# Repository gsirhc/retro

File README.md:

# retro

> **Read-only.** This repo is archived. The browser emulators moved to
> [gsirhc/oac-emu](https://github.com/gsirhc/oac-emu), live at
> <https://gsirhc.github.io/oac-emu/>. This copy is kept for its history.

Recreations of vintage machines, faithful to the real hardware.

## `retroweb/` — the browser emulators

A static site: [`retroweb/index.html`](retroweb/index.html) is the landing page,
each machine is a subdirectory.

| Machine | Source | Deployed at |
|---|---|---|
| **MITS Altair 8800** (Intel 8080, CP/M 2.2, Altair BASIC) | [`retroweb/altair8800/`](retroweb/altair8800/) | `/altair8800/` |

The Altair project is the shared C++ 8080 core (`retroweb/shared/cpu/cpu_i8080`, also
used by Space Invaders) plus 88-2SIO, 88-ACR cassette,
88-DCDD floppy) with a GoogleTest suite, compiled to WebAssembly and wired to an
xterm.js front end in `retroweb/altair8800/web/`. See its
[README](retroweb/altair8800/README.md).

CI (`.github/workflows/deploy-emulator.yml`) runs the C++ and Playwright suites,
stages the site (`retroweb/index.html` at the root, the built front end under
`/altair8800/`), and publishes it to GitHub Pages. It does not deploy a red
build.

## Other directories

`cpu6502`, `commodore64`, `cc65`, `kicad` — earlier / adjacent experiments.

## Provenance

Some earlier commits contained code taken from other emulators. See
[PROVENANCE.md](PROVENANCE.md) for what, and what replaced it.

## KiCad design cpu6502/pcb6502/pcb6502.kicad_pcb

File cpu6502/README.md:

# Programming 6502

## Links

Compiler: <http://www.compilers.de/vasm.html>

Programmer: <https://gitlab.com/DavidGriffith/minipro> (Install with brew)

## Setup

1. Unzip `vasm6502.zip` to .
2. Install minipro (see links above)

## Programming EEPROM

1. Create the assembly file (asm)
2. Compile the assembly:

   `./vasm6502_oldstyle/vasm6502_oldstyle test/ImAlive.asm -dotdir -Fbin`
3. Can check binary with:

   `hexdump -C a.out`
4. Send to programmer:

   `minipro -p AT28C256 -w a.out`
5. You can run:

   `sh compile.sh HellowWorld.asm`

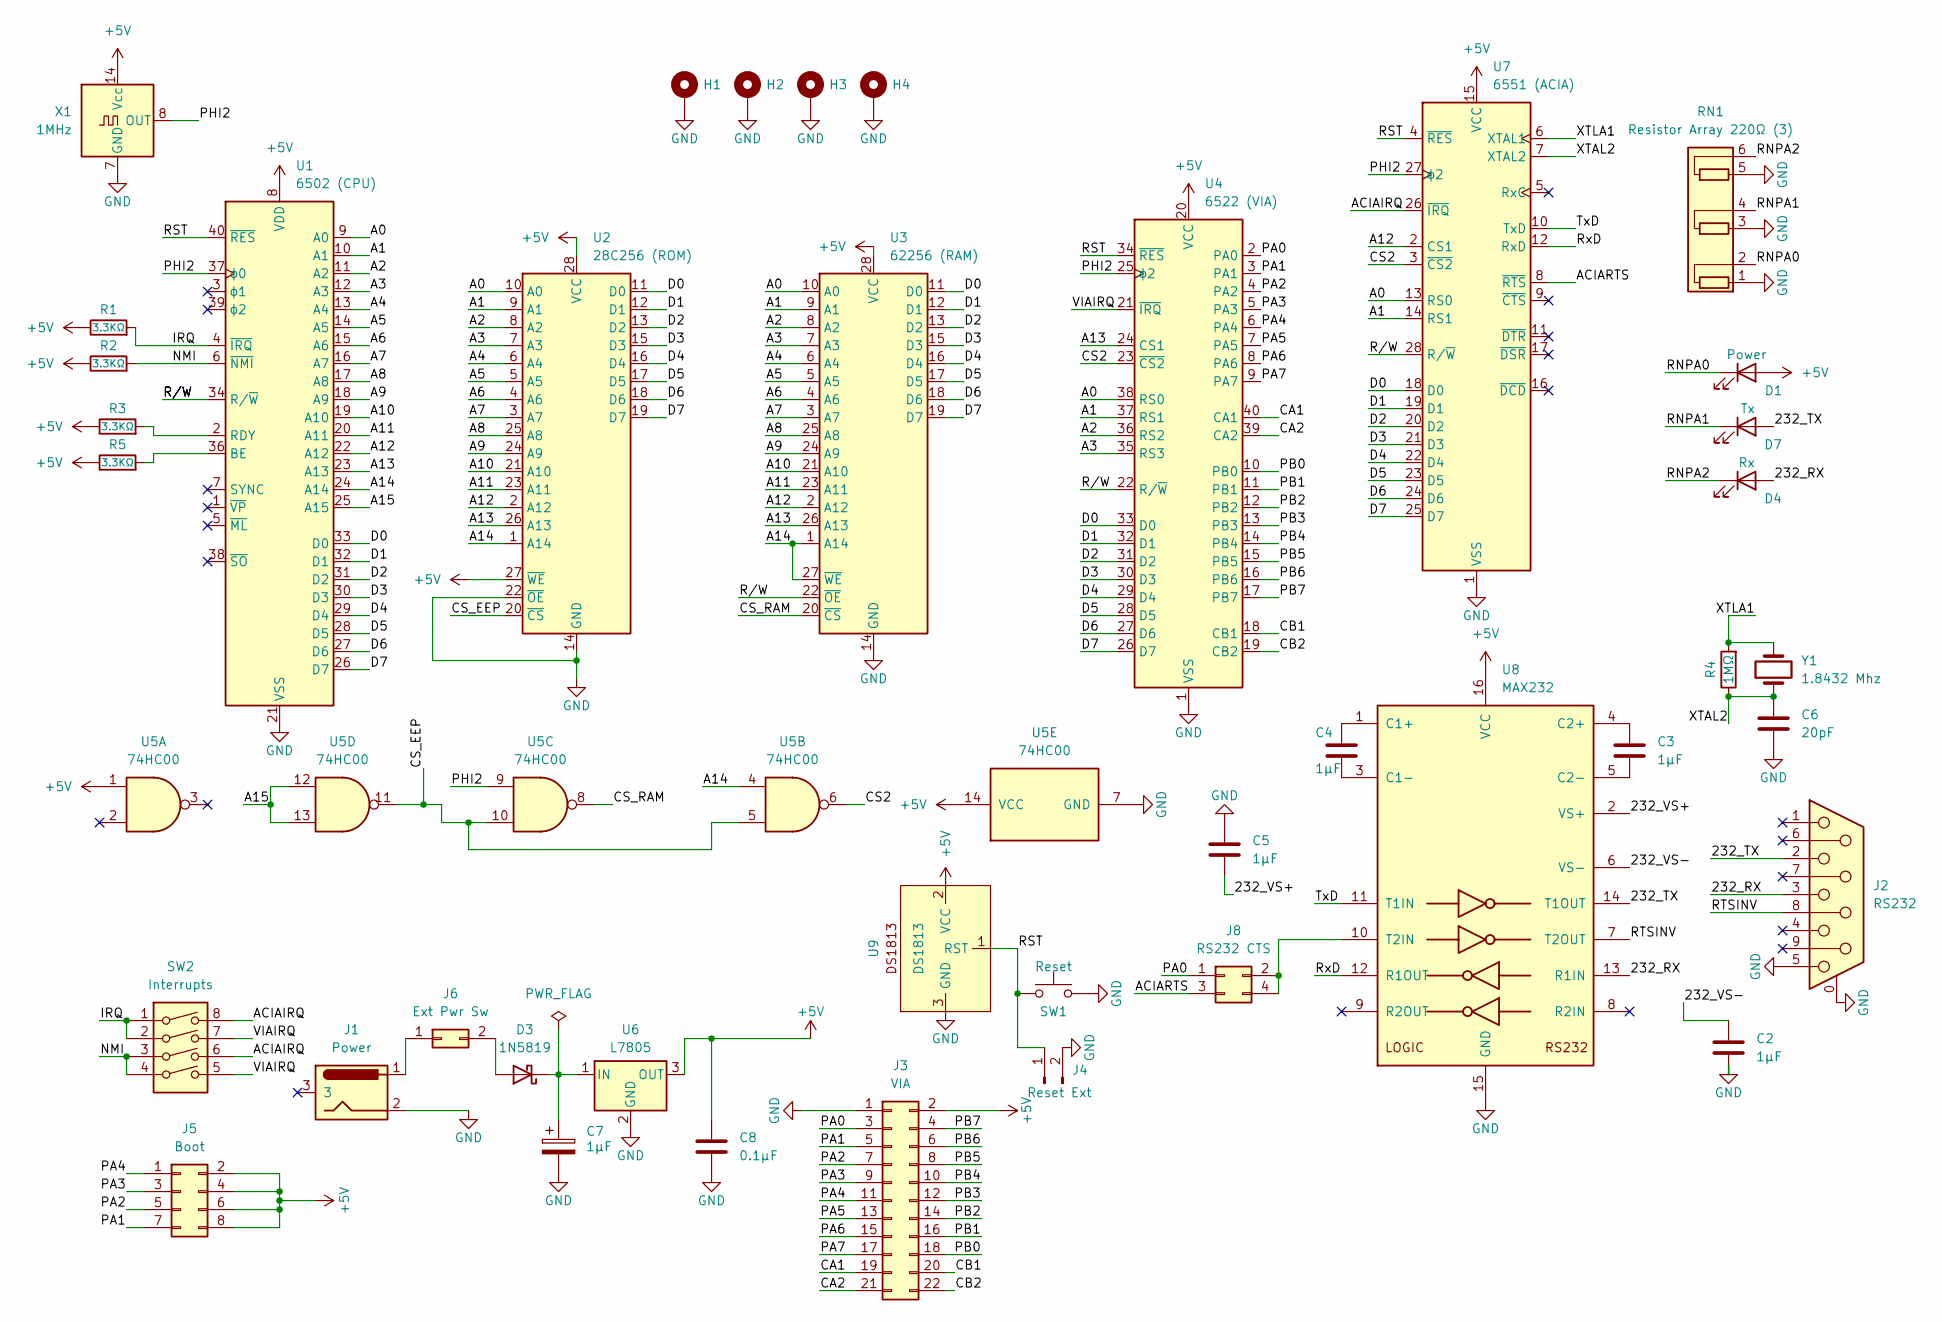
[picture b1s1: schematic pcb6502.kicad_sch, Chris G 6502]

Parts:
C2, C3, C4, C5: 1µF; C_Disc_D5.0mm_W2.5mm_P5.00mm
C6: 20pF; C_Disc_D5.0mm_W2.5mm_P5.00mm
C7: 1µF; CP_Radial_D5.0mm_P2.50mm
C8: 0.1µF; C_Disc_D3.0mm_W1.6mm_P2.50mm
D1: Power; LED_D3.0mm
D3: 1N5819; D_DO-41_SOD81_P10.16mm_Horizontal
D4: Rx; LED_D3.0mm
D7: Tx; LED_D3.0mm
H1, H2, H3, H4: MountingHole_3.2mm_M3_Pad_Via
J1: Power; BarrelJack_Horizontal
J2: RS232; DSUB-9_Male_Horizontal_P2.77x2.84mm_EdgePinOffset4.94mm_Hou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
J3: VIA; PinHeader_2x11_P2.54mm_Vertical
J4: Reset Ext; PinHeader_1x02_P2.54mm_Vertical
J5: Boot; PinHeader_2x04_P2.54mm_Vertical
J6: Ext Pwr Sw; PinHeader_2x01_P2.54mm_Vertical
J8: RS232 CTS; PinHeader_2x02_P2.54mm_Vertical
R1, R2, R3, R5: 3.3KΩ; R_Axial_DIN0204_L3.6mm_D1.6mm_P7.62mm_Horizontal
R4: 1MΩ; R_Axial_DIN0204_L3.6mm_D1.6mm_P7.62mm_Horizontal
RN1: Resistor Array 220Ω (3); R_Array_SIP6
SW1: Reset; SW_TH_Tactile_Omron_B3F-10xx
SW2: Interrupts; SW_DIP_SPSTx04_Slide_9.78x12.34mm_W7.62mm_P2.54mm
U1: 6502 (CPU); DIP-40_W15.24mm_Socket
U2: 28C256 (ROM); DIP-28_600_ZIF_ARIES_28-526-10
U3: 62256 (RAM); DIP-28_W15.24mm_Socket
U4: 6522 (VIA); DIP-40_W15.24mm_Socket
U5: 74HC00; DIP-14_W7.62mm_Socket
U6: L7805; TO-220-3_Horizontal_TabDown
U7: 6551 (ACIA); DIP-28_W15.24mm_Socket
U8: MAX232; DIP-16_W7.62mm_Socket
U9: DS1813; TO-92
X1: 1MHz; Oscillator_DIP-14
Y1: 1.8432 Mhz; Crystal_HC49-4H_Vertical

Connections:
+5V: C8.1, D1.2 (A), J3.2, J5.2, J5.4, J5.6, J5.8, R1.1, R2.1, R3.1, R5.1, U1.8 (VDD), U2.27 (~WE), U2.28 (VCC), U3.28 (VCC), U4.20 (VCC), U5.1, U5.14 (VCC), U6.3 (OUT), U7.15 (VCC), U8.16 (VCC), U9.2 (VCC), X1.14 (Vcc)
/232_RX: D4.2 (A), J2.3, U8.13 (R1IN)
/232_TX: D7.2 (A), J2.2, U8.14 (T1OUT)
/232_VS+: C5.2, U8.2 (VS+)
/232_VS-: C2.1, U8.6 (VS-)
/A0: U1.9 (A0), U2.10 (A0), U3.10 (A0), U4.38 (RS0), U7.13 (RS0)
/A1: U1.10 (A1), U2.9 (A1), U3.9 (A1), U4.37 (RS1), U7.14 (RS1)
/A2: U1.11 (A2), U2.8 (A2), U3.8 (A2), U4.36 (RS2)
/A3: U1.12 (A3), U2.7 (A3), U3.7 (A3), U4.35 (RS3)
/A4: U1.13 (A4), U2.6 (A4), U3.6 (A4)
/A5: U1.14 (A5), U2.5 (A5), U3.5 (A5)
/A6: U1.15 (A6), U2.4 (A6), U3.4 (A6)
/A7: U1.16 (A7), U2.3 (A7), U3.3 (A7)
/A8: U1.17 (A8), U2.25 (A8), U3.25 (A8)
/A9: U1.18 (A9), U2.24 (A9), U3.24 (A9)
/A10: U1.19 (A10), U2.21 (A10), U3.21 (A10)
/A11: U1.20 (A11), U2.23 (A11), U3.23 (A11)
/A12: U1.22 (A12), U2.2 (A12), U3.2 (A12), U7.2 (CS1)
/A13: U1.23 (A13), U2.26 (A13), U3.26 (A13), U4.24 (CS1)
/A14: U1.24 (A14), U2.1 (A14), U3.1 (A14), U3.27 (~WE), U5.4
/A15: U1.25 (A15), U5.12, U5.13
/ACIAIRQ: SW2.6, SW2.8, U7.26 (~IRQ)
/ACIARTS: J8.3, U7.8 (~RTS)
/CA1: J3.19, U4.40 (CA1)
/CA2: J3.21, U4.39 (CA2)
/CB1: J3.20, U4.18 (CB1)
/CB2: J3.22, U4.19 (CB2)
/CS2: U4.23 (~CS2), U5.6, U7.3 (~CS2)
/CS_EEP: U2.20 (~CS), U5.5, U5.10, U5.11
/CS_RAM: U3.20 (~CS), U5.8
/D0: U1.33 (D0), U2.11 (D0), U3.11 (D0), U4.33 (D0), U7.18 (D0)
/D1: U1.32 (D1), U2.12 (D1), U3.12 (D1), U4.32 (D1), U7.19 (D1)
/D2: U1.31 (D2), U2.13 (D2), U3.13 (D2), U4.31 (D2), U7.20 (D2)
/D3: U1.30 (D3), U2.15 (D3), U3.15 (D3), U4.30 (D3), U7.21 (D3)
/D4: U1.29 (D4), U2.16 (D4), U3.16 (D4), U4.29 (D4), U7.22 (D4)
/D5: U1.28 (D5), U2.17 (D5), U3.17 (D5), U4.28 (D5), U7.23 (D5)
/D6: U1.27 (D6), U2.18 (D6), U3.18 (D6), U4.27 (D6), U7.24 (D6)
/D7: U1.26 (D7), U2.19 (D7), U3.19 (D7), U4.26 (D7), U7.25 (D7)
/IRQ: R1.2, SW2.1, SW2.2, U1.4 (~IRQ)
/NMI: R2.2, SW2.3, SW2.4, U1.6 (~NMI)
/PA0: J3.3, J8.1, U4.2 (PA0)
/PA1: J3.5, J5.7, U4.3 (PA1)
/PA2: J3.7, J5.5, U4.4 (PA2)
/PA3: J3.9, J5.3, U4.5 (PA3)
/PA4: J3.11, J5.1, U4.6 (PA4)
/PA5: J3.13, U4.7 (PA5)
/PA6: J3.15, U4.8 (PA6)
/PA7: J3.17, U4.9 (PA7)
/PB0: J3.18, U4.10 (PB0)
/PB1: J3.16, U4.11 (PB1)
/PB2: J3.14, U4.12 (PB2)
/PB3: J3.12, U4.13 (PB3)
/PB4: J3.10, U4.14 (PB4)
/PB5: J3.8, U4.15 (PB5)
/PB6: J3.6, U4.16 (PB6)
/PB7: J3.4, U4.17 (PB7)
/PHI2: U1.37 (ϕ0), U4.25 (ϕ2), U5.9, U7.27 (ϕ2), X1.8 (OUT)
/RNPA0: D1.1 (K), RN1.2 (R1.2)
/RNPA1: D7.1 (K), RN1.4 (R2.2)
/RNPA2: D4.1 (K), RN1.6 (R3.2)
/RST: J4.1, SW1.1, U1.40 (~RES), U4.34 (~RES), U7.4 (~RES), U9.1 (RST)
/RTSINV: J2.8, U8.7 (T2OUT)
/RxD: U7.12 (RxD), U8.12 (R1OUT)
/R/W: U1.34 (R/~W), U3.22 (~OE), U4.22 (R/~W), U7.28 (R/~W)
/TxD: U7.10 (TxD), U8.11 (T1IN)
/VIAIRQ: SW2.5, SW2.7, U4.21 (~IRQ)
/XTAL2: C6.1, R4.1, U7.7 (XTAL2), Y1.1
/XTLA1: R4.2, U7.6 (XTAL1), Y1.2
GND: C2.2, C5.1, C6.2, C7.2, C8.2, H1.1, H2.1, H3.1, H4.1, J1.2, J2.0 (PAD), J2.5, J3.1, J4.2, RN1.1 (R1.1), RN1.3 (R2.1), RN1.5 (R3.1), SW1.2, U1.21 (VSS), U2.14 (GND), U2.22 (~OE), U3.14 (GND), U4.1 (VSS), U5.7 (GND), U6.2 (GND), U7.1 (VSS), U8.15 (GND), U9.3 (GND), X1.7 (GND)
unnamed: D3.2 (A), J6.2
unnamed: C7.1, D3.1 (K), U6.1 (IN)
unnamed: J1.1, J6.1
unnamed: J8.2, J8.4, U8.10 (T2IN)
unnamed: R5.2, U1.36 (BE)
unnamed: R3.2, U1.2 (RDY)
unnamed: C4.1, U8.1 (C1+)
unnamed: C4.2, U8.3 (C1-)
unnamed: C3.1, U8.4 (C2+)
unnamed: C3.2, U8.5 (C2-)

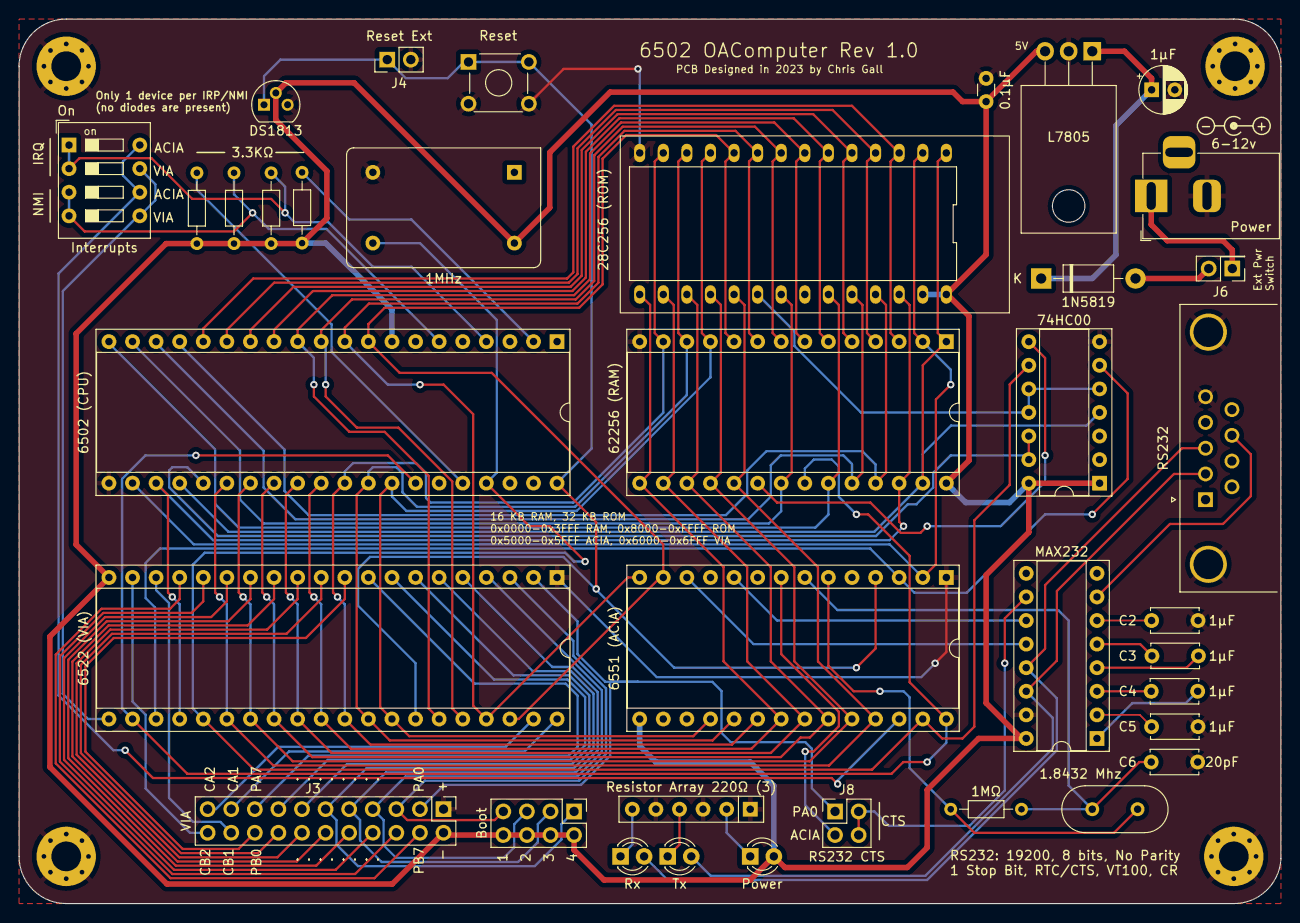
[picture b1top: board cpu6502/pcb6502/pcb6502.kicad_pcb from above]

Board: 2 copper layers, 135.9 x 95.3 mm, 41 parts (0 on the bottom side), 79 nets.

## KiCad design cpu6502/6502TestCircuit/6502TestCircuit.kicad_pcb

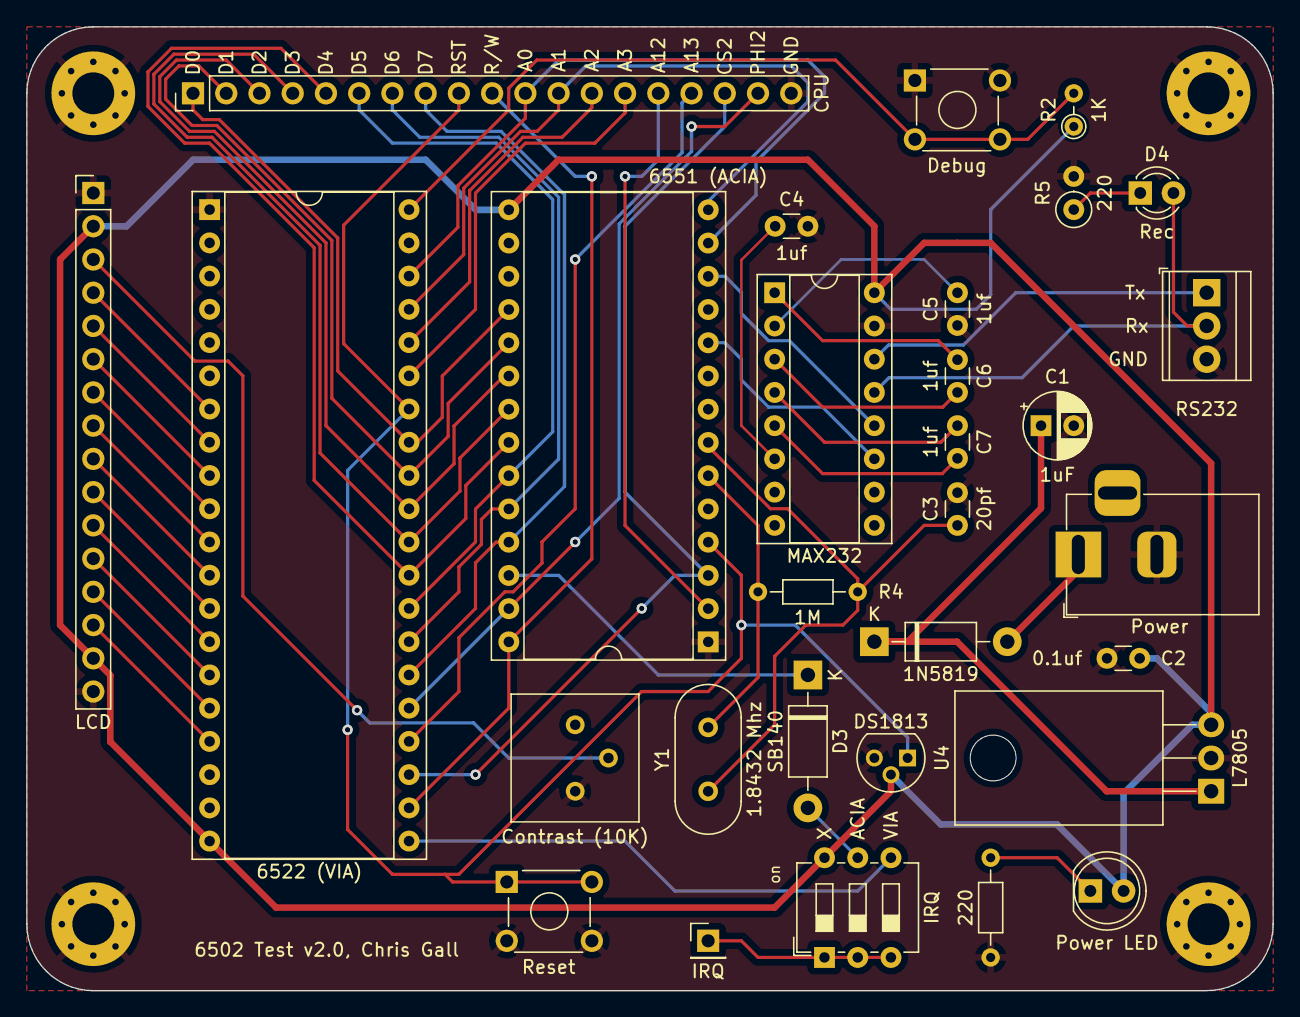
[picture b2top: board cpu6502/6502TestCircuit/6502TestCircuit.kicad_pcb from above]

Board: 2 copper layers, 95.2 x 73.7 mm, 34 parts (0 on the bottom side), 53 nets.

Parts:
C1: 1uF; CP_Radial_D5.0mm_P2.50mm
C2: 0.1uf; C_Disc_D3.0mm_W1.6mm_P2.50mm
C3: 20pf; C_Disc_D3.0mm_W1.6mm_P2.50mm
C4, C5, C6, C7: 1uf; C_Disc_D3.0mm_W1.6mm_P2.50mm
D1: 1N5819; D_DO-41_SOD81_P10.16mm_Horizontal
D2: Power LED; LED_D5.0mm
D3: SB140; D_DO-41_SOD81_P10.16mm_Horizontal
D4: Rec; LED_D3.0mm
H1, H2, H3, H4: MountingHole_3.2mm_M3_Pad_Via
J1: CPU; PinHeader_1x19_P2.54mm_Vertical
J2: IRQ; PinHeader_1x01_P2.54mm_Vertical
J3: LCD; PinHeader_1x16_P2.54mm_Vertical
J4: Power; BarrelJack_Horizontal
J5: RS232; TerminalBlock_TE_282834-3_1x03_P2.54mm_Horizontal
R2: 1K; R_Axial_DIN0204_L3.6mm_D1.6mm_P2.54mm_Vertical
R3: 220; R_Axial_DIN0204_L3.6mm_D1.6mm_P7.62mm_Horizontal
R4: 1M; R_Axial_DIN0204_L3.6mm_D1.6mm_P7.62mm_Horizontal
R5: 220; R_Axial_DIN0207_L6.3mm_D2.5mm_P2.54mm_Vertical
RV2: Contrast (10K); Potentiometer_Bourns_3386P_Vertical
SW2: Debug; SW_TH_Tactile_Omron_B3F-10xx
SW3: Reset; SW_TH_Tactile_Omron_B3F-10xx
SW4: IRQ; SW_DIP_SPSTx03_Slide_6.7x9.18mm_W7.62mm_P2.54mm_LowProfile
U1: 6522 (VIA); DIP-40_W15.24mm_Socket
U4: L7805; TO-220-3_Horizontal_TabDown
U5: DS1813; TO-92
U8: MAX232; DIP-16_W7.62mm_Socket
U9: 6551 (ACIA); DIP-28_W15.24mm_Socket
Y1: 1.8432 Mhz; Crystal_HC49-4H_Vertical

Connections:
+5V: C2.1, D2.2 (A), J3.2, J3.15, R2.1, SW4.6, U1.20 (VCC), U4.3 (OUT), U5.2 (VCC), U8.16 (VCC), U9.15 (VCC)
/232_VS+: C5.2, U8.2 (VS+)
/232_VS-: C4.1, U8.6 (VS-)
/A0: J1.11, U1.38 (RS0), U9.13 (RS0)
/A1: J1.12, U1.37 (RS1), U9.14 (RS1)
/A2: J1.13, U1.36 (RS2)
/A3: J1.14, U1.35 (RS3)
/A12: J1.15, U9.2 (CS1)
/A13: J1.16, U1.24 (CS1)
/ACIAIRQ: D3.2 (A), SW4.5
/CA1: R2.2, SW2.2, U1.40 (CA1)
/CS2: J1.17, U1.23 (~CS2), U9.3 (~CS2)
/D0: J1.1, U1.33 (D0), U9.18 (D0)
/D1: J1.2, U1.32 (D1), U9.19 (D1)
/D2: J1.3, U1.31 (D2), U9.20 (D2)
/D3: J1.4, U1.30 (D3), U9.21 (D3)
/D4: J1.5, U1.29 (D4), U9.22 (D4)
/D5: J1.6, U1.28 (D5), U9.23 (D5)
/D6: J1.7, U1.27 (D6), U9.24 (D6)
/D7: J1.8, U1.26 (D7), U9.25 (D7)
/IRQ: J2.1, SW4.1, SW4.2, SW4.3
/PA5: J3.4, U1.7 (PA5)
/PA6: J3.5, U1.8 (PA6)
/PA7: J3.6, U1.9 (PA7)
/PB0: J3.7, U1.10 (PB0)
/PB1: J3.8, U1.11 (PB1)
/PB2: J3.9, U1.12 (PB2)
/PB3: J3.10, U1.13 (PB3)
/PB4: J3.11, U1.14 (PB4)
/PB5: J3.12, U1.15 (PB5)
/PB6: J3.13, U1.16 (PB6)
/PB7: J3.14, U1.17 (PB7)
/PHI2: J1.18, U1.25 (ϕ2), U9.27 (ϕ2)
/RST: J1.9, SW3.1, U1.34 (~RES), U5.1 (RST), U9.4 (~RES)
/RxD: U8.12 (R1OUT), U9.12 (RxD)
/R/W: J1.10, U1.22 (R/~W), U9.28 (R/~W)
/TxD: U8.11 (T1IN), U9.10 (TxD)
/VIAIRQ: SW4.4, U1.21 (~IRQ)
/XTAL2: C3.1, R4.1, U9.7 (XTAL2), Y1.1
/XTLA1: R4.2, U9.6 (XTAL1), Y1.2
GND: C1.2, C2.2, C3.2, C4.2, C5.1, H1.1, H2.1, H3.1, H4.1, J1.19, J3.1, J3.16, J4.2, J5.3, R3.2, R5.2, RV2.1, SW2.1, SW3.2, U1.1 (VSS), U4.2 (GND), U5.3 (GND), U8.15 (GND), U9.1 (VSS)
unnamed: D1.2 (A), J4.1
unnamed: C1.1, D1.1 (K), U4.1 (IN)
unnamed: D2.1 (K), R3.1
unnamed: D3.1 (K), U9.26 (~IRQ)
unnamed: D4.2 (A), J5.2, U8.13 (R1IN)
unnamed: D4.1 (K), R5.1
unnamed: J3.3, RV2.2
unnamed: J5.1, U8.14 (T1OUT)
unnamed: C6.1, U8.1 (C1+)
unnamed: C6.2, U8.3 (C1-)
unnamed: C7.1, U8.4 (C2+)
unnamed: C7.2, U8.5 (C2-)

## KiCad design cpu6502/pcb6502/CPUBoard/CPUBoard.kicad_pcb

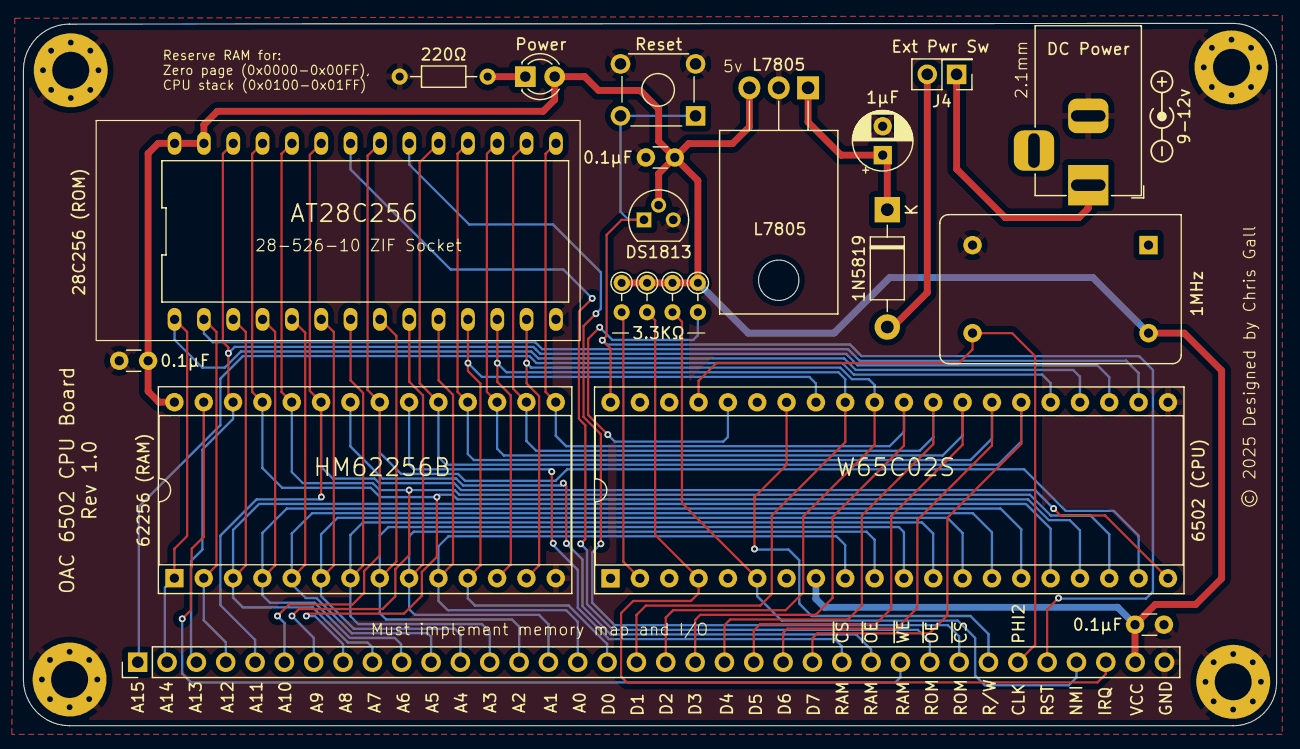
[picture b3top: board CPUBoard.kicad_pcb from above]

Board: 2 copper layers, 108.5 x 60.8 mm, 25 parts (0 on the bottom side), 42 nets.

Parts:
C1: 1µF; CP_Radial_D5.0mm_P2.50mm
C2, C3, C4: 0.1µF; C_Disc_D3.0mm_W1.6mm_P2.50mm
D1: 1N5819; D_DO-41_SOD81_P10.16mm_Horizontal
D2: Power; LED_D3.0mm
H1, H2, H3, H4: MountingHole_3.2mm_M3_Pad_Via
J1: Expansion; PinHeader_1x36_P2.54mm_Vertical
J3: DC Power; BarrelJack_Horizontal
J4: Ext Pwr Sw; PinHeader_2x01_P2.54mm_Vertical
R1, R2, R3, R4: 3.3KΩ; R_Axial_DIN0204_L3.6mm_D1.6mm_P2.54mm_Vertical
R7: 220Ω; R_Axial_DIN0204_L3.6mm_D1.6mm_P7.62mm_Horizontal
SW1: Reset; SW_TH_Tactile_Omron_B3F-10xx
U2: 6502 (CPU); DIP-40_W15.24mm_Socket
U3: 28C256 (ROM); DIP-28_600_ZIF_ARIES_28-526-10
U4: L7805; TO-220-3_Horizontal_TabDown
U5: 62256 (RAM); DIP-28_W15.24mm_Socket
U6: DS1813; TO-92
X1: 1MHz; Oscillator_DIP-14

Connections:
+5V: C2.1, C3.1, C4.2, D2.2 (A), J1.35, R1.1, R2.1, R3.1, R4.1, U2.8 (VDD), U3.27 (~WE), U3.28 (VCC), U4.3 (OUT), U5.28 (VCC), U6.2 (VCC), X1.14 (Vcc)
/A0: J1.16, U2.9 (A0), U3.10 (A0), U5.10 (A0)
/A1: J1.15, U2.10 (A1), U3.9 (A1), U5.9 (A1)
/A2: J1.14, U2.11 (A2), U3.8 (A2), U5.8 (A2)
/A3: J1.13, U2.12 (A3), U3.7 (A3), U5.7 (A3)
/A4: J1.12, U2.13 (A4), U3.6 (A4), U5.6 (A4)
/A5: J1.11, U2.14 (A5), U3.5 (A5), U5.5 (A5)
/A6: J1.10, U2.15 (A6), U3.4 (A6), U5.4 (A6)
/A7: J1.9, U2.16 (A7), U3.3 (A7), U5.3 (A7)
/A8: J1.8, U2.17 (A8), U3.25 (A8), U5.25 (A8)
/A9: J1.7, U2.18 (A9), U3.24 (A9), U5.24 (A9)
/A10: J1.6, U2.19 (A10), U3.21 (A10), U5.21 (A10)
/A11: J1.5, U2.20 (A11), U3.23 (A11), U5.23 (A11)
/A12: J1.4, U2.22 (A12), U3.2 (A12), U5.2 (A12)
/A13: J1.3, U2.23 (A13), U3.26 (A13), U5.26 (A13)
/A14: J1.2, U2.24 (A14), U3.1 (A14), U5.1 (A14)
/A15: J1.1, U2.25 (A15)
/D0: J1.17, U2.33 (D0), U3.11 (D0), U5.11 (D0)
/D1: J1.18, U2.32 (D1), U3.12 (D1), U5.12 (D1)
/D2: J1.19, U2.31 (D2), U3.13 (D2), U5.13 (D2)
/D3: J1.20, U2.30 (D3), U3.15 (D3), U5.15 (D3)
/D4: J1.21, U2.29 (D4), U3.16 (D4), U5.16 (D4)
/D5: J1.22, U2.28 (D5), U3.17 (D5), U5.17 (D5)
/D6: J1.23, U2.27 (D6), U3.18 (D6), U5.18 (D6)
/D7: J1.24, U2.26 (D7), U3.19 (D7), U5.19 (D7)
/IRQ: J1.34, R1.2, U2.4 (~IRQ)
/NMI: J1.33, R2.2, U2.6 (~NMI)
/PHI2: J1.31, U2.37 (ϕ0), X1.8 (OUT)
/RNPA0: D2.1 (K), R7.1
/RST: J1.32, SW1.1, U2.40 (~RES), U6.1 (RST)
/R/W: J1.30, U2.34 (R/~W)
/~RAMCS: J1.25, U5.20 (~CS)
/~RAMOE: J1.26, U5.22 (~OE)
/~RAMWE: J1.27, U5.27 (~WE)
/~ROMCS: J1.29, U3.20 (~CS)
/~ROMOE: J1.28, U3.22 (~OE)
GND: C1.2, C2.2, C3.2, C4.1, H1.1, H2.1, H3.1, H4.1, J1.36, J3.2, R7.2, SW1.2, U2.21 (VSS), U3.14 (GND), U4.2 (GND), U5.14 (GND), U6.3 (GND), X1.7 (GND)
unnamed: D1.2 (A), J4.2
unnamed: C1.1, D1.1 (K), U4.1 (IN)
unnamed: J3.1, J4.1
unnamed: R4.2, U2.36 (BE)
unnamed: R3.2, U2.2 (RDY)

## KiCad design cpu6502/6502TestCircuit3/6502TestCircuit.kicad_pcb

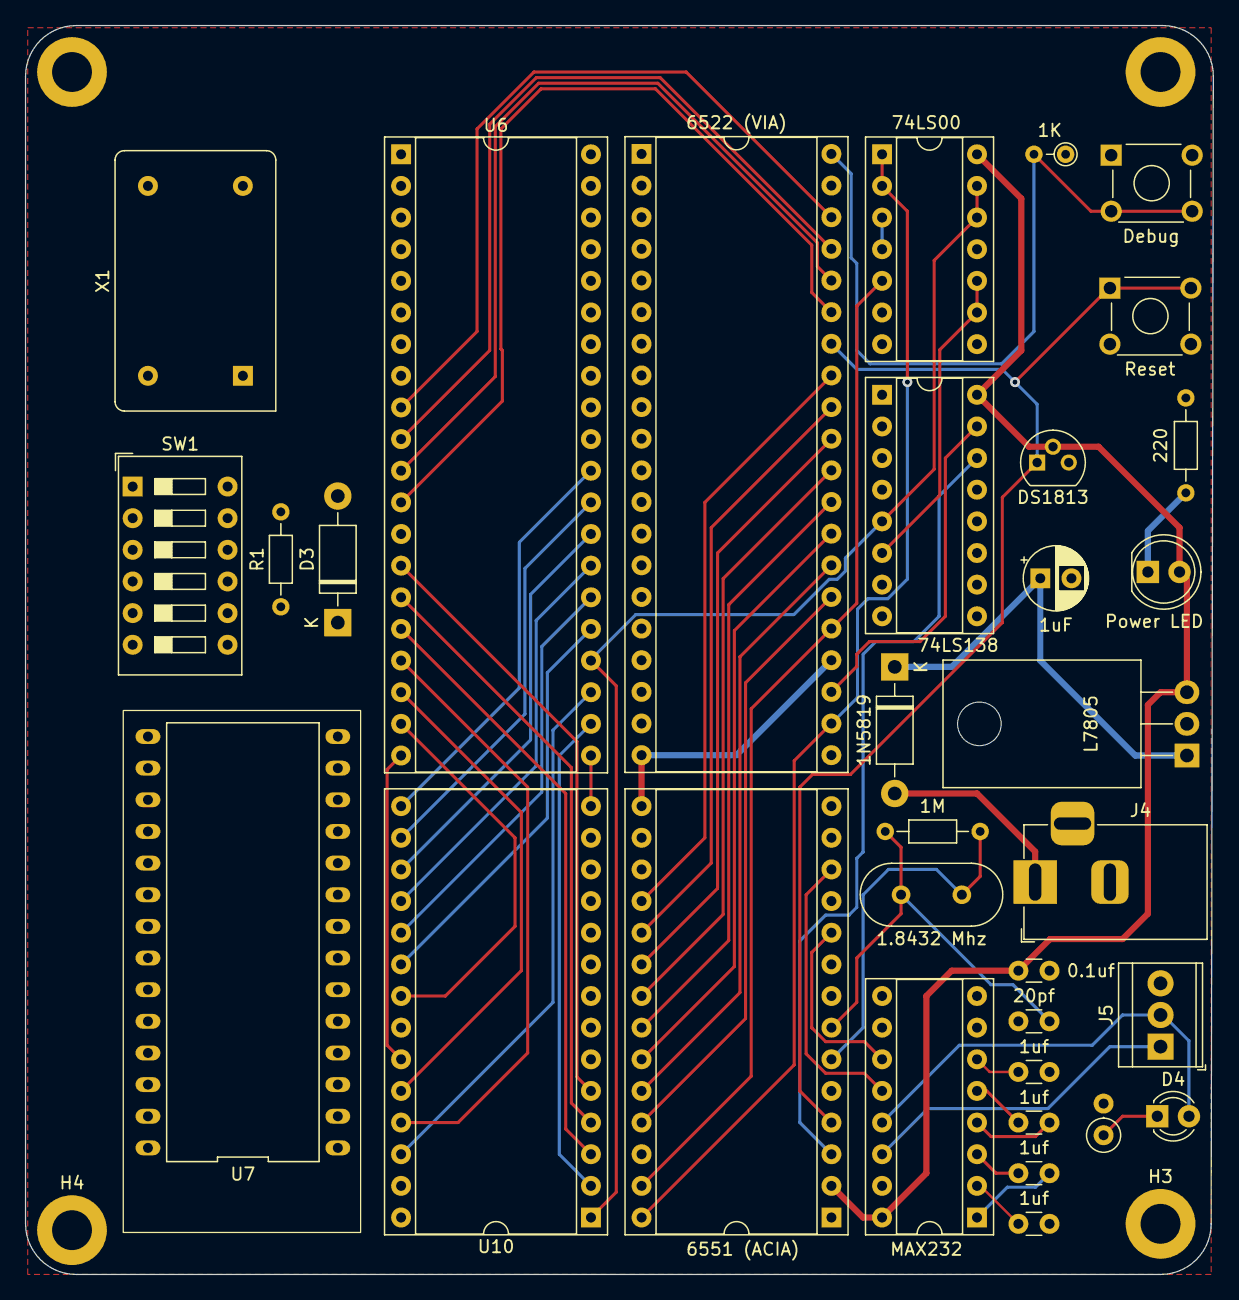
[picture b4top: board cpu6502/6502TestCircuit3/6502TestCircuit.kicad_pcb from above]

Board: 2 copper layers, 95.3 x 100.3 mm, 37 parts (0 on the bottom side), 58 nets.

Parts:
C1: 1uF; CP_Radial_D5.0mm_P2.50mm
C2: 0.1uf; C_Disc_D3.0mm_W1.6mm_P2.50mm
C3: 20pf; C_Disc_D3.0mm_W1.6mm_P2.50mm
C4, C5, C6, C7: 1uf; C_Disc_D3.0mm_W1.6mm_P2.50mm
D1: 1N5819; D_DO-41_SOD81_P10.16mm_Horizontal
D2: Power LED; LED_D5.0mm
D3: SB140; D_DO-41_SOD81_P10.16mm_Horizontal
D4: Rec; LED_D3.0mm
H1, H2, H3, H4: MountingHole_3.2mm_M3_DIN965_Pad
J4: Power; BarrelJack_Horizontal
J5: RS232; TerminalBlock_TE_282834-3_1x03_P2.54mm_Horizontal
R1: 1K; R_Axial_DIN0204_L3.6mm_D1.6mm_P7.62mm_Horizontal
R2: 1K; R_Axial_DIN0204_L3.6mm_D1.6mm_P2.54mm_Vertical
R3: 220; R_Axial_DIN0204_L3.6mm_D1.6mm_P7.62mm_Horizontal
R4: 1M; R_Axial_DIN0204_L3.6mm_D1.6mm_P7.62mm_Horizontal
R5: 220; R_Axial_DIN0207_L6.3mm_D2.5mm_P2.54mm_Vertical
SW1: IRQ/NMI; SW_DIP_SPSTx06_Slide_9.78x17.42mm_W7.62mm_P2.54mm
SW2: Debug; SW_TH_Tactile_Omron_B3F-10xx
SW3: Reset; SW_TH_Tactile_Omron_B3F-10xx
U1: 6522 (VIA); DIP-40_W15.24mm_Socket
U2: 74LS00; DIP-14_W7.62mm_Socket
U3: 74LS138; DIP-16_W7.62mm_Socket
U4: L7805; TO-220-3_Horizontal_TabDown
U5: DS1813; TO-92
U6: 6502 (CPU); DIP-40_W15.24mm_Socket
U7: 28C256 (ROM); DIP-28_600_ZIF_ARIES_28-526-10
U8: MAX232; DIP-16_W7.62mm_Socket
U9: 6551 (ACIA); DIP-28_W15.24mm_Socket
U10: 62256 (RAM); DIP-28_W15.24mm_Socket
X1: 1MHz; Oscillator_DIP-14
Y1: 1.8432 Mhz; Crystal_HC49-4H_Vertical

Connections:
+5V: C2.1, D2.2 (A), R1.1, R2.1, SW1.7, SW1.12, U1.20 (VCC), U1.24 (CS1), U2.14 (VCC), U3.16 (VCC), U4.3 (OUT), U5.2 (VCC), U6.6 (~NMI), U6.8 (VDD), U6.36 (BE), U7.27 (~WE), U7.28 (VCC), U8.16 (VCC), U9.2 (CS1), U9.15 (VCC), U10.28 (VCC), X1.14 (Vcc)
/232_VS+: C5.2, U8.2 (VS+)
/232_VS-: C4.1, U8.6 (VS-)
/A0: U1.38 (RS0), U6.9 (A0), U7.10 (A0), U9.13 (RS0), U10.10 (A0)
/A1: U1.37 (RS1), U6.10 (A1), U7.9 (A1), U9.14 (RS1), U10.9 (A1)
/A2: U1.36 (RS2), U6.11 (A2), U7.8 (A2), U10.8 (A2)
/A3: U1.35 (RS3), U6.12 (A3), U7.7 (A3), U10.7 (A3)
/A4: U6.13 (A4), U7.6 (A4), U10.6 (A4)
/A5: U6.14 (A5), U7.5 (A5), U10.5 (A5)
/A6: U6.15 (A6), U7.4 (A6), U10.4 (A6)
/A7: U6.16 (A7), U7.3 (A7), U10.3 (A7)
/A8: U6.17 (A8), U7.25 (A8), U10.25 (A8)
/A9: U6.18 (A9), U7.24 (A9), U10.24 (A9)
/A10: U3.1 (A0), U6.19 (A10), U7.21 (A10), U10.21 (A10)
/A11: U3.2 (A1), U6.20 (A11), U7.23 (A11), U10.23 (A11)
/A12: U3.3 (A2), U6.22 (A12), U7.2 (A12), U10.2 (A12)
/A13: U3.4 (E1), U6.23 (A13), U7.26 (A13), U10.26 (A13)
/A14: U2.12, U2.13, U3.5 (E2), U6.24 (A14), U7.1 (A14), U10.1 (A14)
/A15: U2.9, U2.10, U3.6 (E3), U6.25 (A15), U10.20 (~CS)
/ACIAIRQ: D3.2 (A), SW1.9, SW1.11
/CA1: R2.2, SW2.2, U1.40 (CA1)
/D0: U1.33 (D0), U6.33 (D0), U7.11 (D0), U9.18 (D0), U10.11 (D0)
/D1: U1.32 (D1), U6.32 (D1), U7.12 (D1), U9.19 (D1), U10.12 (D1)
/D2: U1.31 (D2), U6.31 (D2), U7.13 (D2), U9.20 (D2), U10.13 (D2)
/D3: U1.30 (D3), U6.30 (D3), U7.15 (D3), U9.21 (D3), U10.15 (D3)
/D4: U1.29 (D4), U6.29 (D4), U7.16 (D4), U9.22 (D4), U10.16 (D4)
/D5: U1.28 (D5), U6.28 (D5), U7.17 (D5), U9.23 (D5), U10.17 (D5)
/D6: U1.27 (D6), U6.27 (D6), U7.18 (D6), U9.24 (D6), U10.18 (D6)
/D7: U1.26 (D7), U6.26 (D7), U7.19 (D7), U9.25 (D7), U10.19 (D7)
/IOACIA: U3.14 (O1), U9.3 (~CS2)
/IOVIA: U1.23 (~CS2), U3.15 (O0)
/IRQ: SW1.1, SW1.2, SW1.3, U6.4 (~IRQ)
/NMI: SW1.4, SW1.5, SW1.6
/PHI2: U1.25 (ϕ2), U2.5, U6.37 (ϕ0), U9.27 (ϕ2), X1.8 (OUT)
/RAMOE: U2.3, U2.4, U10.22 (~OE)
/RAMWE: U2.6, U10.27 (~WE)
/ROMCE: U2.8, U7.20 (~CS)
/ROMOE: U2.11, U7.22 (~OE)
/RST: SW3.1, U1.34 (~RES), U5.1 (RST), U6.40 (~RES), U9.4 (~RES)
/RxD: U8.12 (R1OUT), U9.12 (RxD)
/R/W: U1.22 (R/~W), U2.1, U2.2, U6.34 (R/~W), U9.28 (R/~W)
/TxD: U8.11 (T1IN), U9.10 (TxD)
/VIAIRQ: SW1.8, SW1.10, U1.21 (~IRQ)
/XTAL2: C3.1, R4.1, U9.7 (XTAL2), Y1.1
/XTLA1: R4.2, U9.6 (XTAL1), Y1.2
GND: C1.2, C2.2, C3.2, C4.2, C5.1, H1.1, H2.1, H3.1, H4.1, J4.2, J5.3, R3.2, R5.2, SW2.1, SW3.2, U1.1 (VSS), U2.7 (GND), U3.8 (GND), U4.2 (GND), U5.3 (GND), U6.21 (VSS), U7.14 (GND), U8.15 (GND), U9.1 (VSS), U10.14 (GND), X1.7 (GND)
unnamed: D1.2 (A), J4.1
unnamed: C1.1, D1.1 (K), U4.1 (IN)
unnamed: D2.1 (K), R3.1
unnamed: D3.1 (K), U9.26 (~IRQ)
unnamed: D4.2 (A), J5.2, U8.13 (R1IN)
unnamed: D4.1 (K), R5.1
unnamed: J5.1, U8.14 (T1OUT)
unnamed: R1.2, U6.2 (RDY)
unnamed: C6.1, U8.1 (C1+)
unnamed: C6.2, U8.3 (C1-)
unnamed: C7.1, U8.4 (C2+)
unnamed: C7.2, U8.5 (C2-)

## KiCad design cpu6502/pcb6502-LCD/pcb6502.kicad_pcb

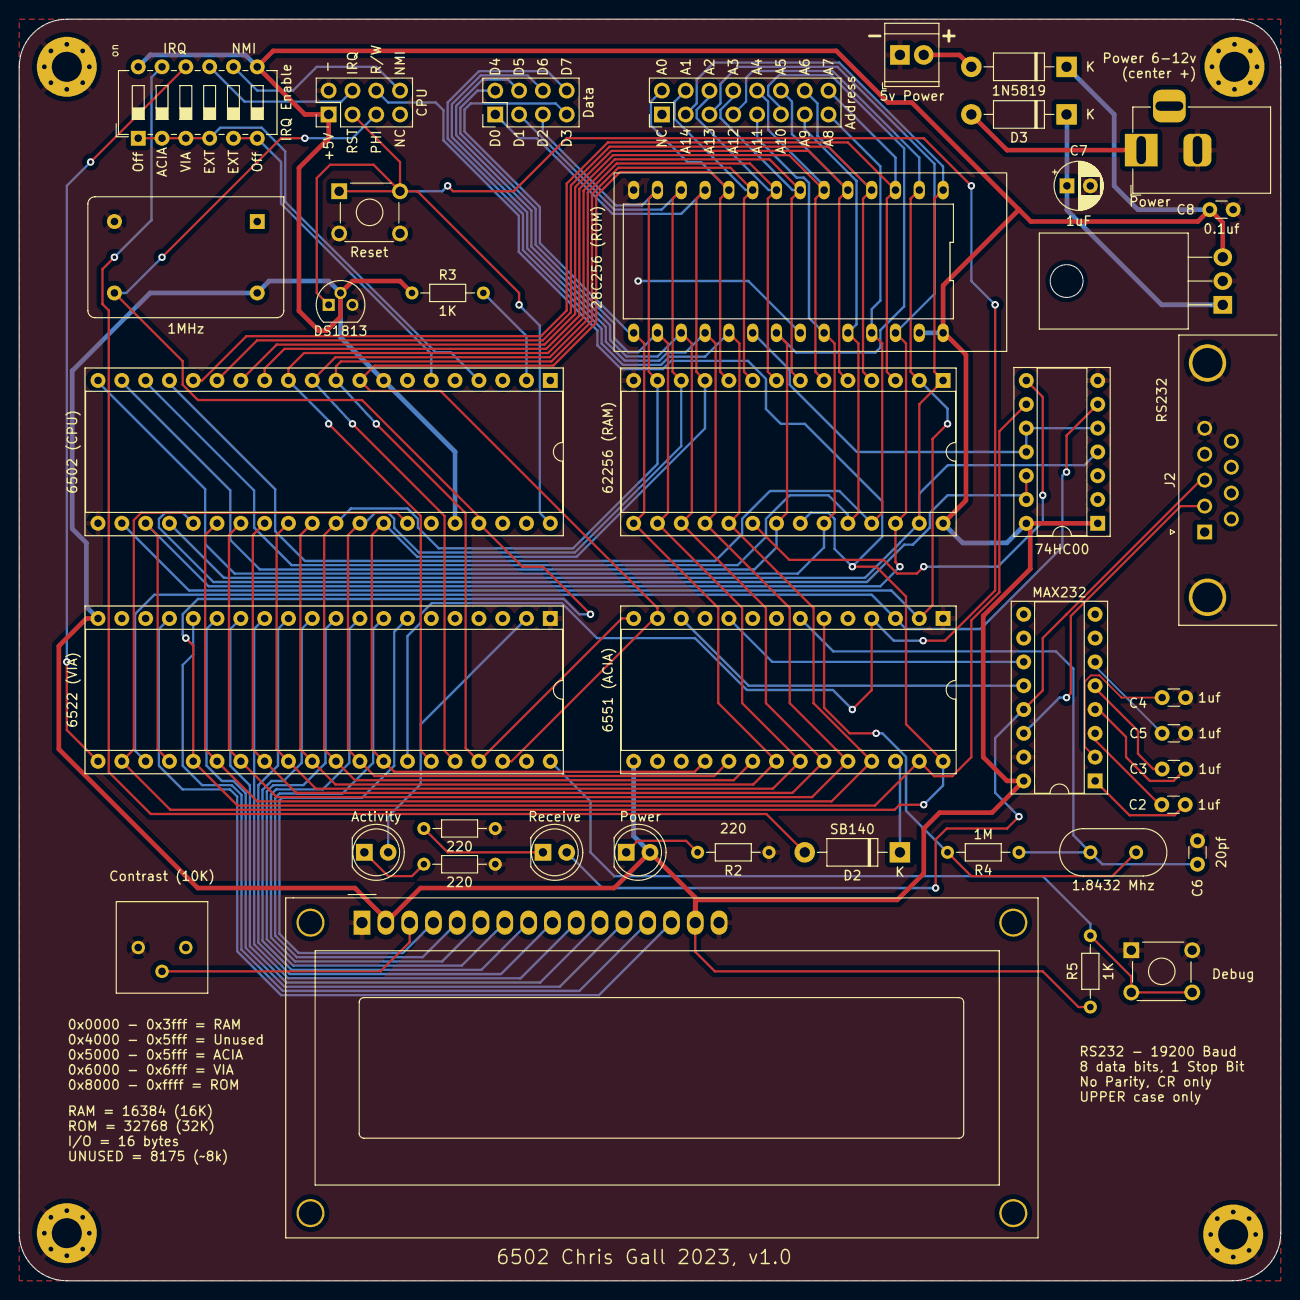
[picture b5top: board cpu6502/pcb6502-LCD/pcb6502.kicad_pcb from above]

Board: 2 copper layers, 134.6 x 134.6 mm, 45 parts (0 on the bottom side), 72 nets.

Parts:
C2, C3, C4, C5: 1uf; C_Disc_D3.0mm_W1.6mm_P2.50mm
C6: 20pf; C_Disc_D3.0mm_W1.6mm_P2.50mm
C7: 1uF; CP_Radial_D5.0mm_P2.50mm
C8: 0.1uf; C_Disc_D3.0mm_W1.6mm_P2.50mm
D1: Power; LED_D5.0mm
D2: SB140; D_DO-41_SOD81_P10.16mm_Horizontal
D3, D6: 1N5819; D_DO-41_SOD81_P10.16mm_Horizontal
D4: Receive; LED_D5.0mm
D5: Activity; LED_D5.0mm
DS1: HY1602E; WC1602A
H1, H2, H3, H4: MountingHole_3.2mm_M3_Pad_Via
J1: Power; BarrelJack_Horizontal
J2: RS232; DSUB-9_Male_Horizontal_P2.77x2.84mm_EdgePinOffset4.94mm_Hou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
J3: 5v Power; TerminalBlock_TE_282834-2_1x02_P2.54mm_Horizontal
J6: Address; PinHeader_2x08_P2.54mm_Vertical
J7: Data; PinHeader_2x04_P2.54mm_Vertical
J8: CPU; PinHeader_2x04_P2.54mm_Vertical
R1, R2, R6: 220; R_Axial_DIN0204_L3.6mm_D1.6mm_P7.62mm_Horizontal
R3, R5: 1K; R_Axial_DIN0204_L3.6mm_D1.6mm_P7.62mm_Horizontal
R4: 1M; R_Axial_DIN0204_L3.6mm_D1.6mm_P7.62mm_Horizontal
RV1: Contrast (10K); Potentiometer_Bourns_3386P_Vertical
SW1: Reset; SW_TH_Tactile_Omron_B3F-10xx
SW2: IRQ Enable; SW_DIP_SPSTx06_Slide_6.7x16.8mm_W7.62mm_P2.54mm_LowProfile
SW3: Debug; SW_TH_Tactile_Omron_B3F-10xx
U1: 6502 (CPU); DIP-40_W15.24mm_Socket
U2: 28C256 (ROM); DIP-28_600_ZIF_ARIES_28-526-10
U3: 62256 (RAM); DIP-28_W15.24mm_Socket
U4: 6522 (VIA); DIP-40_W15.24mm_Socket
U5: 74HC00; DIP-14_W7.62mm_Socket
U6: L7805; TO-220-3_Horizontal_TabDown
U7: 6551 (ACIA); DIP-28_W15.24mm_Socket
U8: MAX232; DIP-16_W7.62mm_Socket
U9: DS1813; TO-92
X1: 1MHz; Oscillator_DIP-14
Y1: 1.8432 Mhz; Crystal_HC49-4H_Vertical

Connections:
+5V: C8.1, D1.2 (A), D6.1 (K), DS1.2 (VDD), DS1.15 (LEDA), J8.1, R3.1, R5.1, SW2.7, SW2.12, U1.8 (VDD), U1.36 (BE), U2.27 (~WE), U2.28 (VCC), U3.28 (VCC), U4.20 (VCC), U5.1, U5.14 (VCC), U6.3 (OUT), U7.15 (VCC), U8.16 (VCC), U9.2 (VCC), X1.14 (Vcc)
/232_VS+: C4.2, U8.2 (VS+)
/232_VS-: C5.1, U8.6 (VS-)
/A0: J6.2, U1.9 (A0), U2.10 (A0), U3.10 (A0), U4.38 (RS0), U7.13 (RS0)
/A1: J6.4, U1.10 (A1), U2.9 (A1), U3.9 (A1), U4.37 (RS1), U7.14 (RS1)
/A2: J6.6, U1.11 (A2), U2.8 (A2), U3.8 (A2), U4.36 (RS2)
/A3: J6.8, U1.12 (A3), U2.7 (A3), U3.7 (A3), U4.35 (RS3)
/A4: J6.10, U1.13 (A4), U2.6 (A4), U3.6 (A4)
/A5: J6.12, U1.14 (A5), U2.5 (A5), U3.5 (A5)
/A6: J6.14, U1.15 (A6), U2.4 (A6), U3.4 (A6)
/A7: J6.16, U1.16 (A7), U2.3 (A7), U3.3 (A7)
/A8: J6.15, U1.17 (A8), U2.25 (A8), U3.25 (A8)
/A9: J6.13, U1.18 (A9), U2.24 (A9), U3.24 (A9)
/A10: J6.11, U1.19 (A10), U2.21 (A10), U3.21 (A10)
/A11: J6.9, U1.20 (A11), U2.23 (A11), U3.23 (A11)
/A12: J6.7, U1.22 (A12), U2.2 (A12), U3.2 (A12), U7.2 (CS1)
/A13: J6.5, U1.23 (A13), U2.26 (A13), U3.26 (A13), U4.24 (CS1)
/A14: J6.3, U1.24 (A14), U2.1 (A14), U3.1 (A14), U3.27 (~WE), U5.4
/A15: U1.25 (A15), U5.12, U5.13
/ACIAIRQ: D2.2 (A), SW2.11
/CA1: R5.2, SW3.2, U4.40 (CA1)
/CS2: U4.23 (~CS2), U5.6, U7.3 (~CS2)
/CS_EEP: U2.20 (~CS), U5.5, U5.10, U5.11
/CS_RAM: U3.20 (~CS), U5.8
/D0: J7.1, U1.33 (D0), U2.11 (D0), U3.11 (D0), U4.33 (D0), U7.18 (D0)
/D1: J7.3, U1.32 (D1), U2.12 (D1), U3.12 (D1), U4.32 (D1), U7.19 (D1)
/D2: J7.5, U1.31 (D2), U2.13 (D2), U3.13 (D2), U4.31 (D2), U7.20 (D2)
/D3: J7.7, U1.30 (D3), U2.15 (D3), U3.15 (D3), U4.30 (D3), U7.21 (D3)
/D4: J7.2, U1.29 (D4), U2.16 (D4), U3.16 (D4), U4.29 (D4), U7.22 (D4)
/D5: J7.4, U1.28 (D5), U2.17 (D5), U3.17 (D5), U4.28 (D5), U7.23 (D5)
/D6: J7.6, U1.27 (D6), U2.18 (D6), U3.18 (D6), U4.27 (D6), U7.24 (D6)
/D7: J7.8, U1.26 (D7), U2.19 (D7), U3.19 (D7), U4.26 (D7), U7.25 (D7)
/ExtIRQ: J8.4, SW2.9
/ExtNMI: J8.8, SW2.8
/IRQ: SW2.1, SW2.2, SW2.3, SW2.4, U1.4 (~IRQ)
/NMI: SW2.5, SW2.6, U1.6 (~NMI)
/PA0: D5.2 (A), U4.2 (PA0)
/PA5: DS1.4 (RS), U4.7 (PA5)
/PA6: DS1.5 (R/~W), U4.8 (PA6)
/PA7: DS1.6 (E), U4.9 (PA7)
/PB0: DS1.7 (DB0), U4.10 (PB0)
/PB1: DS1.8 (DB1), U4.11 (PB1)
/PB2: DS1.9 (DB2), U4.12 (PB2)
/PB3: DS1.10 (DB3), U4.13 (PB3)
/PB4: DS1.11 (DB4), U4.14 (PB4)
/PB5: DS1.12 (DB5), U4.15 (PB5)
/PB6: DS1.13 (DB6), U4.16 (PB6)
/PB7: DS1.14 (DB7), U4.17 (PB7)
/PHI2: J8.5, U1.37 (ϕ0), U4.25 (ϕ2), U5.9, U7.27 (ϕ2), X1.8 (OUT)
/RST: J8.3, SW1.1, U1.40 (~RES), U4.34 (~RES), U7.4 (~RES), U9.1 (RST)
/RxD: U7.12 (RxD), U8.12 (R1OUT)
/R/W: J8.6, U1.34 (R/~W), U3.22 (~OE), U4.22 (R/~W), U7.28 (R/~W)
/TxD: U7.10 (TxD), U8.11 (T1IN)
/VIAIRQ: SW2.10, U4.21 (~IRQ)
/XTAL2: C6.1, R4.1, U7.7 (XTAL2), Y1.1
/XTLA1: R4.2, U7.6 (XTAL1), Y1.2
GND: C4.1, C5.2, C6.2, C7.2, C8.2, DS1.1 (VSS), DS1.16 (LEDK), H1.1, H2.1, H3.1, H4.1, J1.2, J2.0 (PAD), J2.5, J3.1, J8.2, R1.2, R2.2, R6.2, RV1.1, SW1.2, SW3.1, U1.21 (VSS), U2.14 (GND), U2.22 (~OE), U3.14 (GND), U4.1 (VSS), U5.7 (GND), U6.2 (GND), U7.1 (VSS), U8.15 (GND), U9.3 (GND), X1.7 (GND)
unnamed: D1.1 (K), R2.1
unnamed: D2.1 (K), U7.26 (~IRQ)
unnamed: D3.2 (A), J1.1
unnamed: C7.1, D3.1 (K), U6.1 (IN)
unnamed: D4.2 (A), J2.3, U8.13 (R1IN)
unnamed: D4.1 (K), R1.1
unnamed: D5.1 (K), R6.1
unnamed: D6.2 (A), J3.2
unnamed: DS1.3 (Vo), RV1.2
unnamed: R3.2, U1.2 (RDY)
unnamed: C2.1, U8.1 (C1+)
unnamed: C2.2, U8.3 (C1-)
unnamed: C3.1, U8.4 (C2+)
unnamed: C3.2, U8.5 (C2-)
unnamed: J2.2, U8.14 (T1OUT)

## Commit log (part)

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2023-07-24 initial add cpu6502
2023-07-24 Add compile.sh to contain commands
2023-08-04 Add asm, first pass at 6502 PCB (not complete
2023-08-04 connect more pins 6502 PCB
2023-08-08 start to add rs232
2023-08-09 finish rs232, re-layour PCB
2023-08-11 routed PCB!
2023-08-11 add ground
2023-08-11 save for redesign
2023-08-12 Finished the PCB
2023-08-15 Finalizing pcb
2023-08-15 Cleanup routes
2023-08-18 add dip switches to pcb, testing rs232 programs
2023-08-18 forgot to save previous
2023-08-18 add test circuit for 6502
2023-08-18 Sent test circuit to PCBWay
2023-08-18 pcb 6502 from 4 layers to 2 layers
2023-08-20 RS232 finally works!!!!!!!!!!!!!
2023-08-26 PCB: Add RS232 RCV LED, get pours connected, CODE: checkpoint
2023-08-27 tweaks
2023-09-01 update PCB with debug button, other cleanup, add Wozmon to cgOS and get it working!
2023-09-08 code changes (wip), set test PCB 2.0 to PCBway
2023-09-22 checkpoint, most significantly OS works!!
2023-09-23 checkpoint - OS mostly working, need to refactor
2023-09-27 check point, OS refactor
2023-09-29 PCB 99.9999% ready to be built (without LCD)
2023-09-30 check point, upgrading OS....eeeeek!
2023-09-30 check point again
2023-10-11 everything is working well! OS still wip but pretty good
2023-10-30 check point
2025-03-05 add msbasic
2025-03-07 move old oacOS to old and tar.gz it
2025-03-11 fix reset
2025-03-11 basic working without input buffer
2025-03-12 input buffer works!
2025-03-12 basic startup messages, boot menu, wozmon input buffer
2025-03-13 good state! its usable (but never finished)
2025-03-18 check points, works-ish
2025-03-23 rs232 nmi / cts, circuit close to done
2025-03-23 basic is odd
2025-03-24 more basic progs
2025-03-28 pcb updates
2025-03-29 dialed in zeropage and inputbuffer length
    PCB CPU BOARD SENT WOOOO HOOO!!
    tweaked basic tokens
2025-03-29 ascii art---terrible
2025-03-29 folder reorg
2025-03-29 wozmon works now with backspace also move buffer to cfg, move stuf around
2025-03-30 refactor, messing around

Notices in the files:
cpu6502/pcb6502/CPUBoard/CPUBoard.kicad_pcb:
© 2025 Designed by Chris Gall
